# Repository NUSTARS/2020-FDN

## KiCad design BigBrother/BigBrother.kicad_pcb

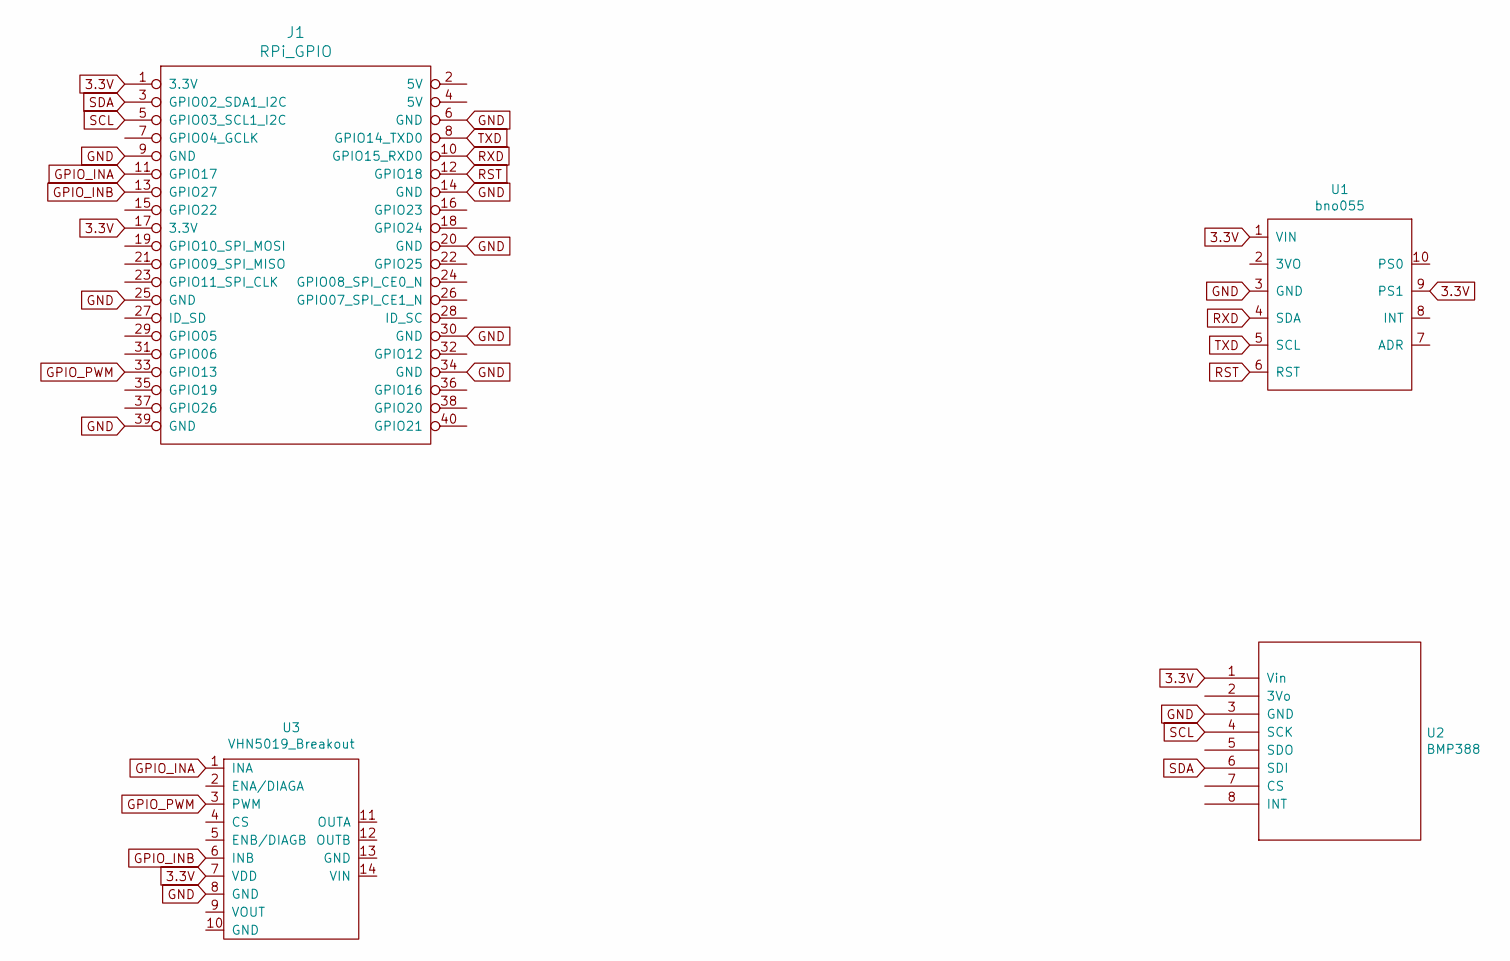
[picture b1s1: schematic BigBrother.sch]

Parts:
J1: RPi_GPIO; RPI_Zero
U1: bno055
U2: BMP388
U3: VHN5019_Breakout; VNH5019_breakout

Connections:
3.3V: J1.1 (3.3V), J1.17 (3.3V), U1.1 (VIN), U1.9 (PS1), U2.1 (Vin), U3.7 (VDD)
GND: J1.6 (GND), J1.9 (GND), J1.14 (GND), J1.20 (GND), J1.25 (GND), J1.30 (GND), J1.34 (GND), J1.39 (GND), U1.3 (GND), U2.3 (GND), U3.8 (GND)
GPIO_INA: J1.11 (GPIO17), U3.1 (INA)
GPIO_INB: J1.13 (GPIO27), U3.6 (INB)
GPIO_PWM: J1.33 (GPIO13), U3.3 (PWM)
RST: J1.12 (GPIO18), U1.6 (RST)
RXD: J1.10 (GPIO15_RXD0), U1.4 (SDA)
SCL: J1.5 (GPIO03_SCL1_I2C), U2.4 (SCK)
SDA: J1.3 (GPIO02_SDA1_I2C), U2.6 (SDI)
TXD: J1.8 (GPIO14_TXD0), U1.5 (SCL)

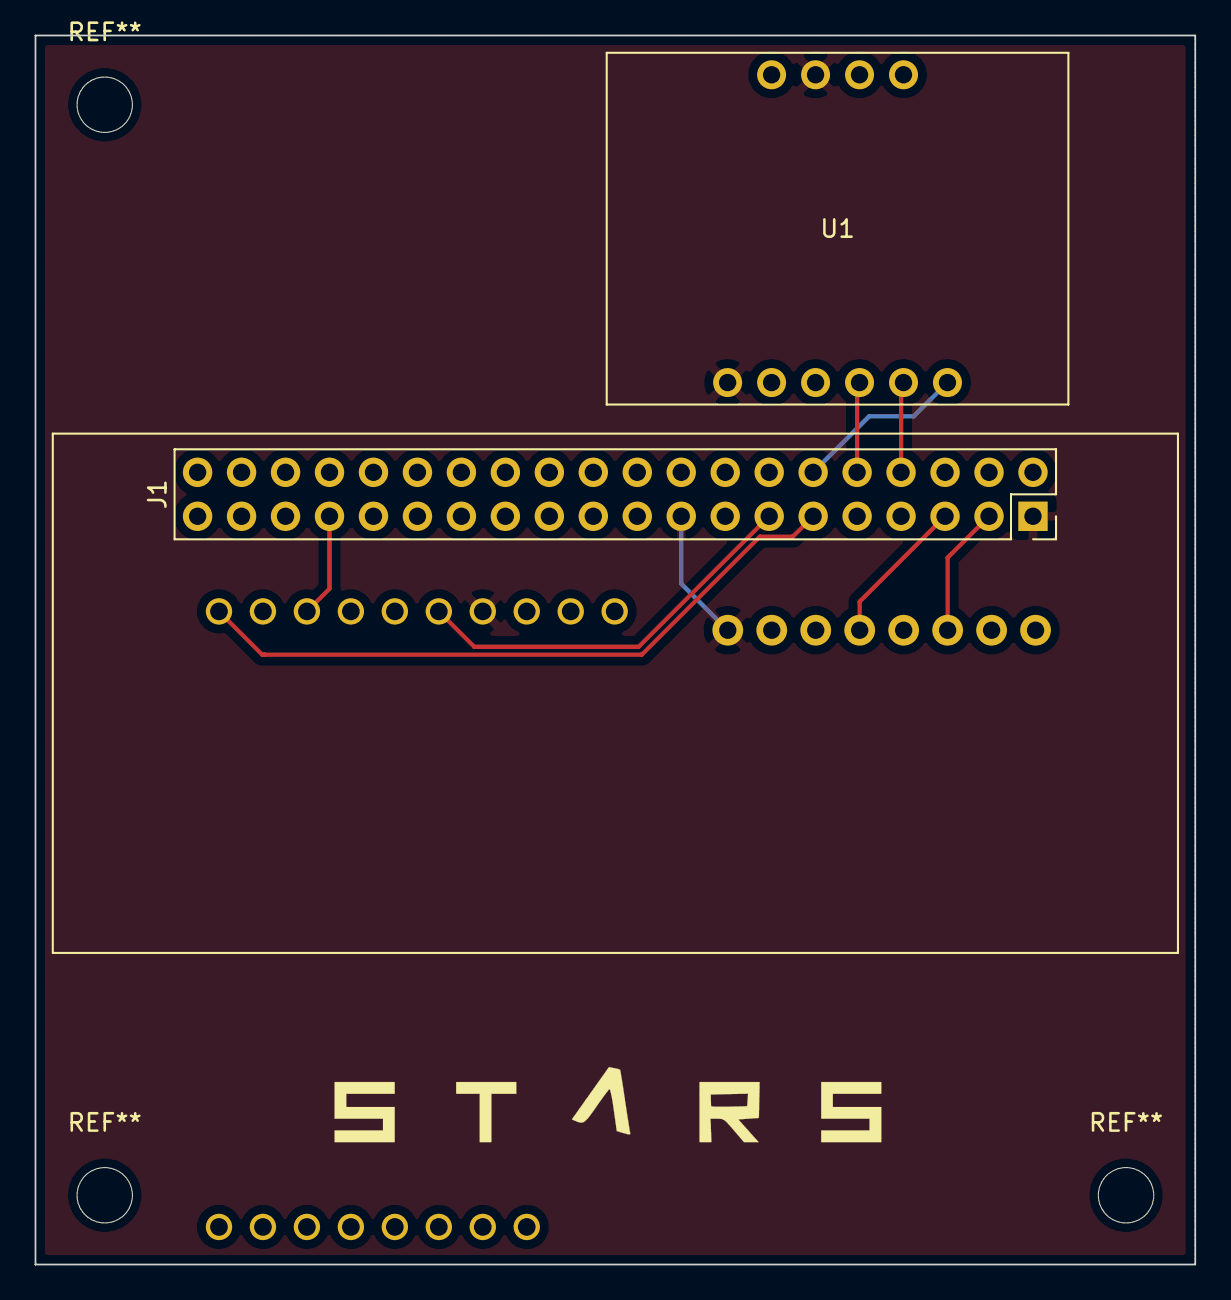
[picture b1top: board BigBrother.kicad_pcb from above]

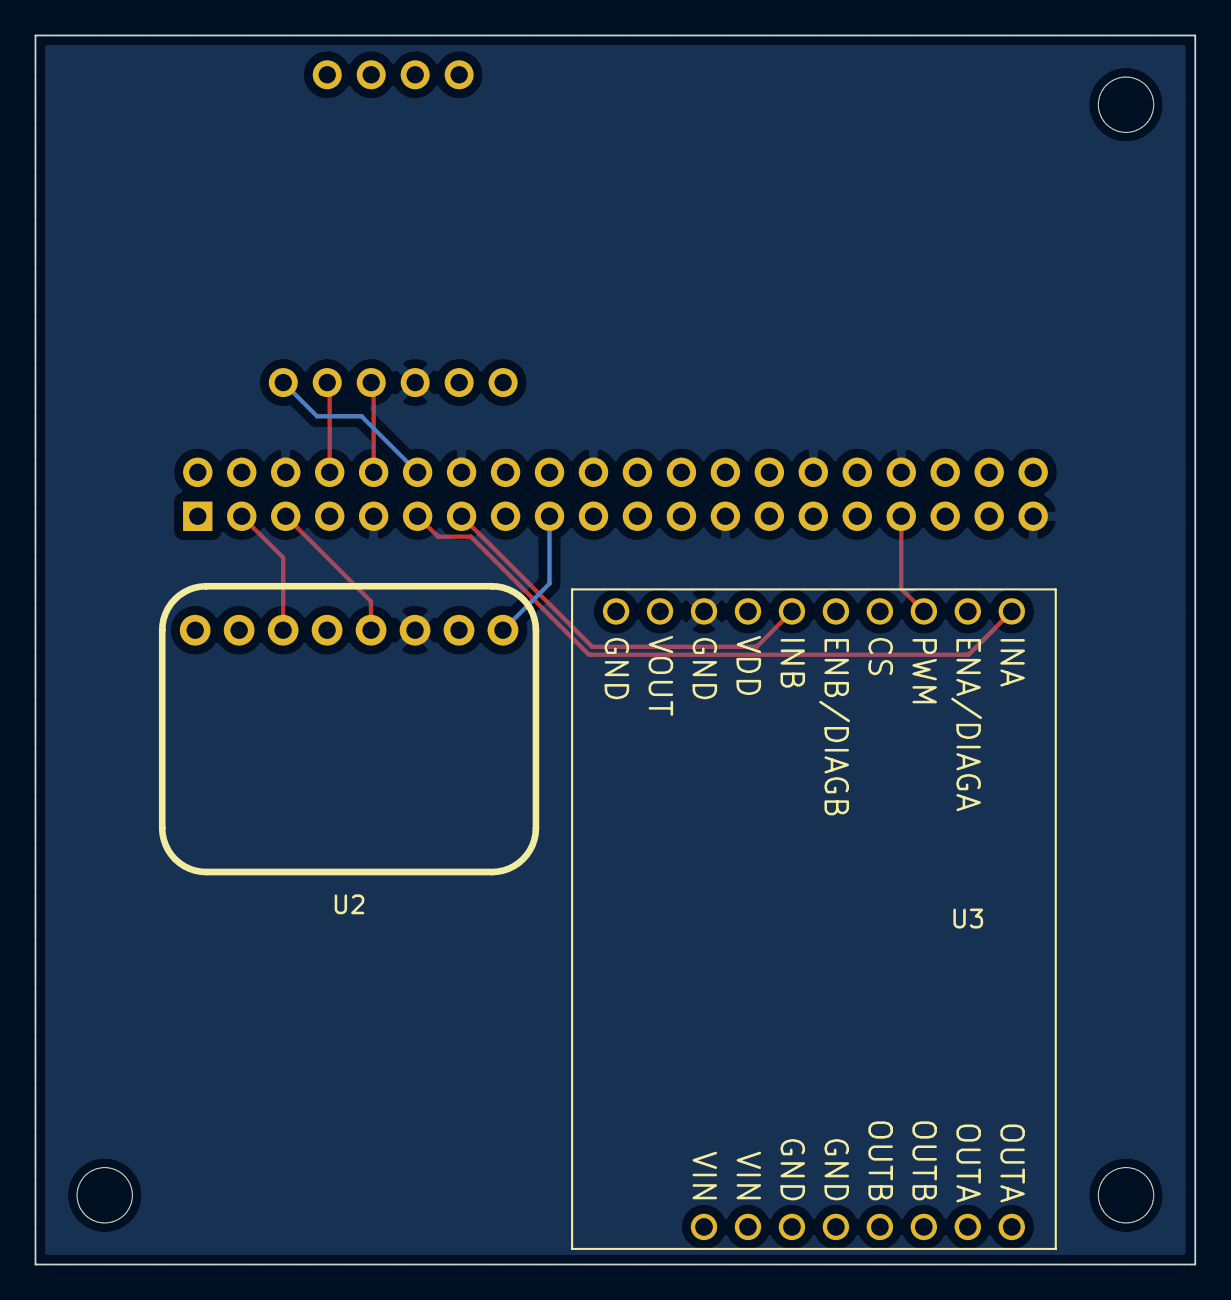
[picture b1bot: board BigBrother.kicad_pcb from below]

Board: 2 copper layers, 67.0 x 71.0 mm, 4 parts (2 on the bottom side), 10 nets.

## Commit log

2020-01-26 add libs dir & BMP388 Schematic
2020-01-26 Create BNO055.lib
    BNO055 Library
    Andrew Laeuger
2020-02-02 BNO055_schematic
2020-02-16 Start BigBrother
2020-02-16 BigBrother Update
2020-02-16 footprint added
2020-02-17 Board updates
2020-02-22 Some footprintz
2020-02-26 Boarddddd
2020-02-28 Board!! maybe done!!!
2020-03-06 I forgot RST
2020-03-08 Gerber
2020-03-10 Mounting holes
